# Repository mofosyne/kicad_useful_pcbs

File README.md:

# kicad_useful_pcbs

Various small pcb boards that may be of use for various projects

## Ec11 Horizontal Breakout Board

This was created for https://github.com/mofosyne/roTec_pcb to make it easier to attach an encoder and also have some debouncing.

- [Schematic PDF](ec11_horizontal_breakout_board/documentation/ec11_horizontal_breakout_board_schematic.pdf)
- [Bill of Materials](ec11_horizontal_breakout_board/documentation/ec11_horizontal_breakout_board_bom.csv)
- [Fabrication File](ec11_horizontal_breakout_board/ec11_horizontal_breakout_board_fabrication.zip)

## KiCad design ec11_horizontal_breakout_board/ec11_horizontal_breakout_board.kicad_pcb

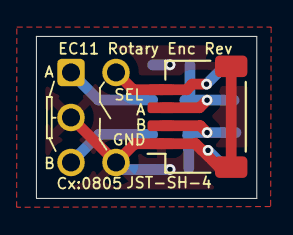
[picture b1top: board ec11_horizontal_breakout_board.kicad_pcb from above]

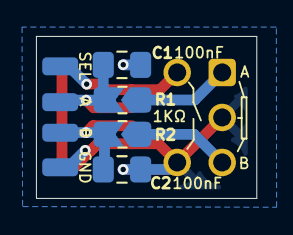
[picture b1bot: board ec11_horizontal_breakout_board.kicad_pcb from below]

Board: 2 copper layers, 12.2 x 9.0 mm, 10 parts (8 on the bottom side), 6 nets.

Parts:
C1, C2: 100nF; C_0805_2012Metric_Pad1.18x1.45mm_HandSolder
J1, J2, J3, J4: Conn_01x01_Socket; SolderWirePad_1x01_SMD_1x2mm
J50: JST-SH-4; JST_SH_SM04B-SRSS-TB_1x04-1MP_P1.00mm_Horizontal
R1, R2: 1K; R_0805_2012Metric_Pad1.20x1.40mm_HandSolder_And_Jumper
SW3: RotaryEncoder_Switch; RotaryEncoder_Bourns_Horizontal_PEC12R-2x17F-Sxxxx

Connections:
/A: C1.1, J3.1, J50.3, R1.2
/B: C2.1, J2.1, J50.2, R2.2
/ENC_A: R1.1, SW3.A
/ENC_B: R2.1, SW3.B
/ENC_PUSH: J4.1, J50.4, SW3.S1
GND: C1.2, C2.2, J1.1, J50.1, J50.MP (MountPin), SW3.C, SW3.S2

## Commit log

2025-12-26 ec11 horizontal readme added
2025-12-26 hw: create fab zips
2025-12-29 Add filtering to ec11 encoder breakout. Also change to makefile builder
2026-01-01 Ec11 breakout encoder Rev3
